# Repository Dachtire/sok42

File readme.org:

#+TITLE: Split Optical Keyboard
[[./hardware/image/00-overview.jpg]]

* Hardware
** MCU
gd32vf103cbt6

** Case
Stacked acrylic or 3d print

** Switch
gateron ks-22, ks-15

* Firmware
Custom firmware with usb, uart, led basic function

* Thanks
[[https://discord.com/channels/715975244896272618/715975245336412346][Optical Future]]

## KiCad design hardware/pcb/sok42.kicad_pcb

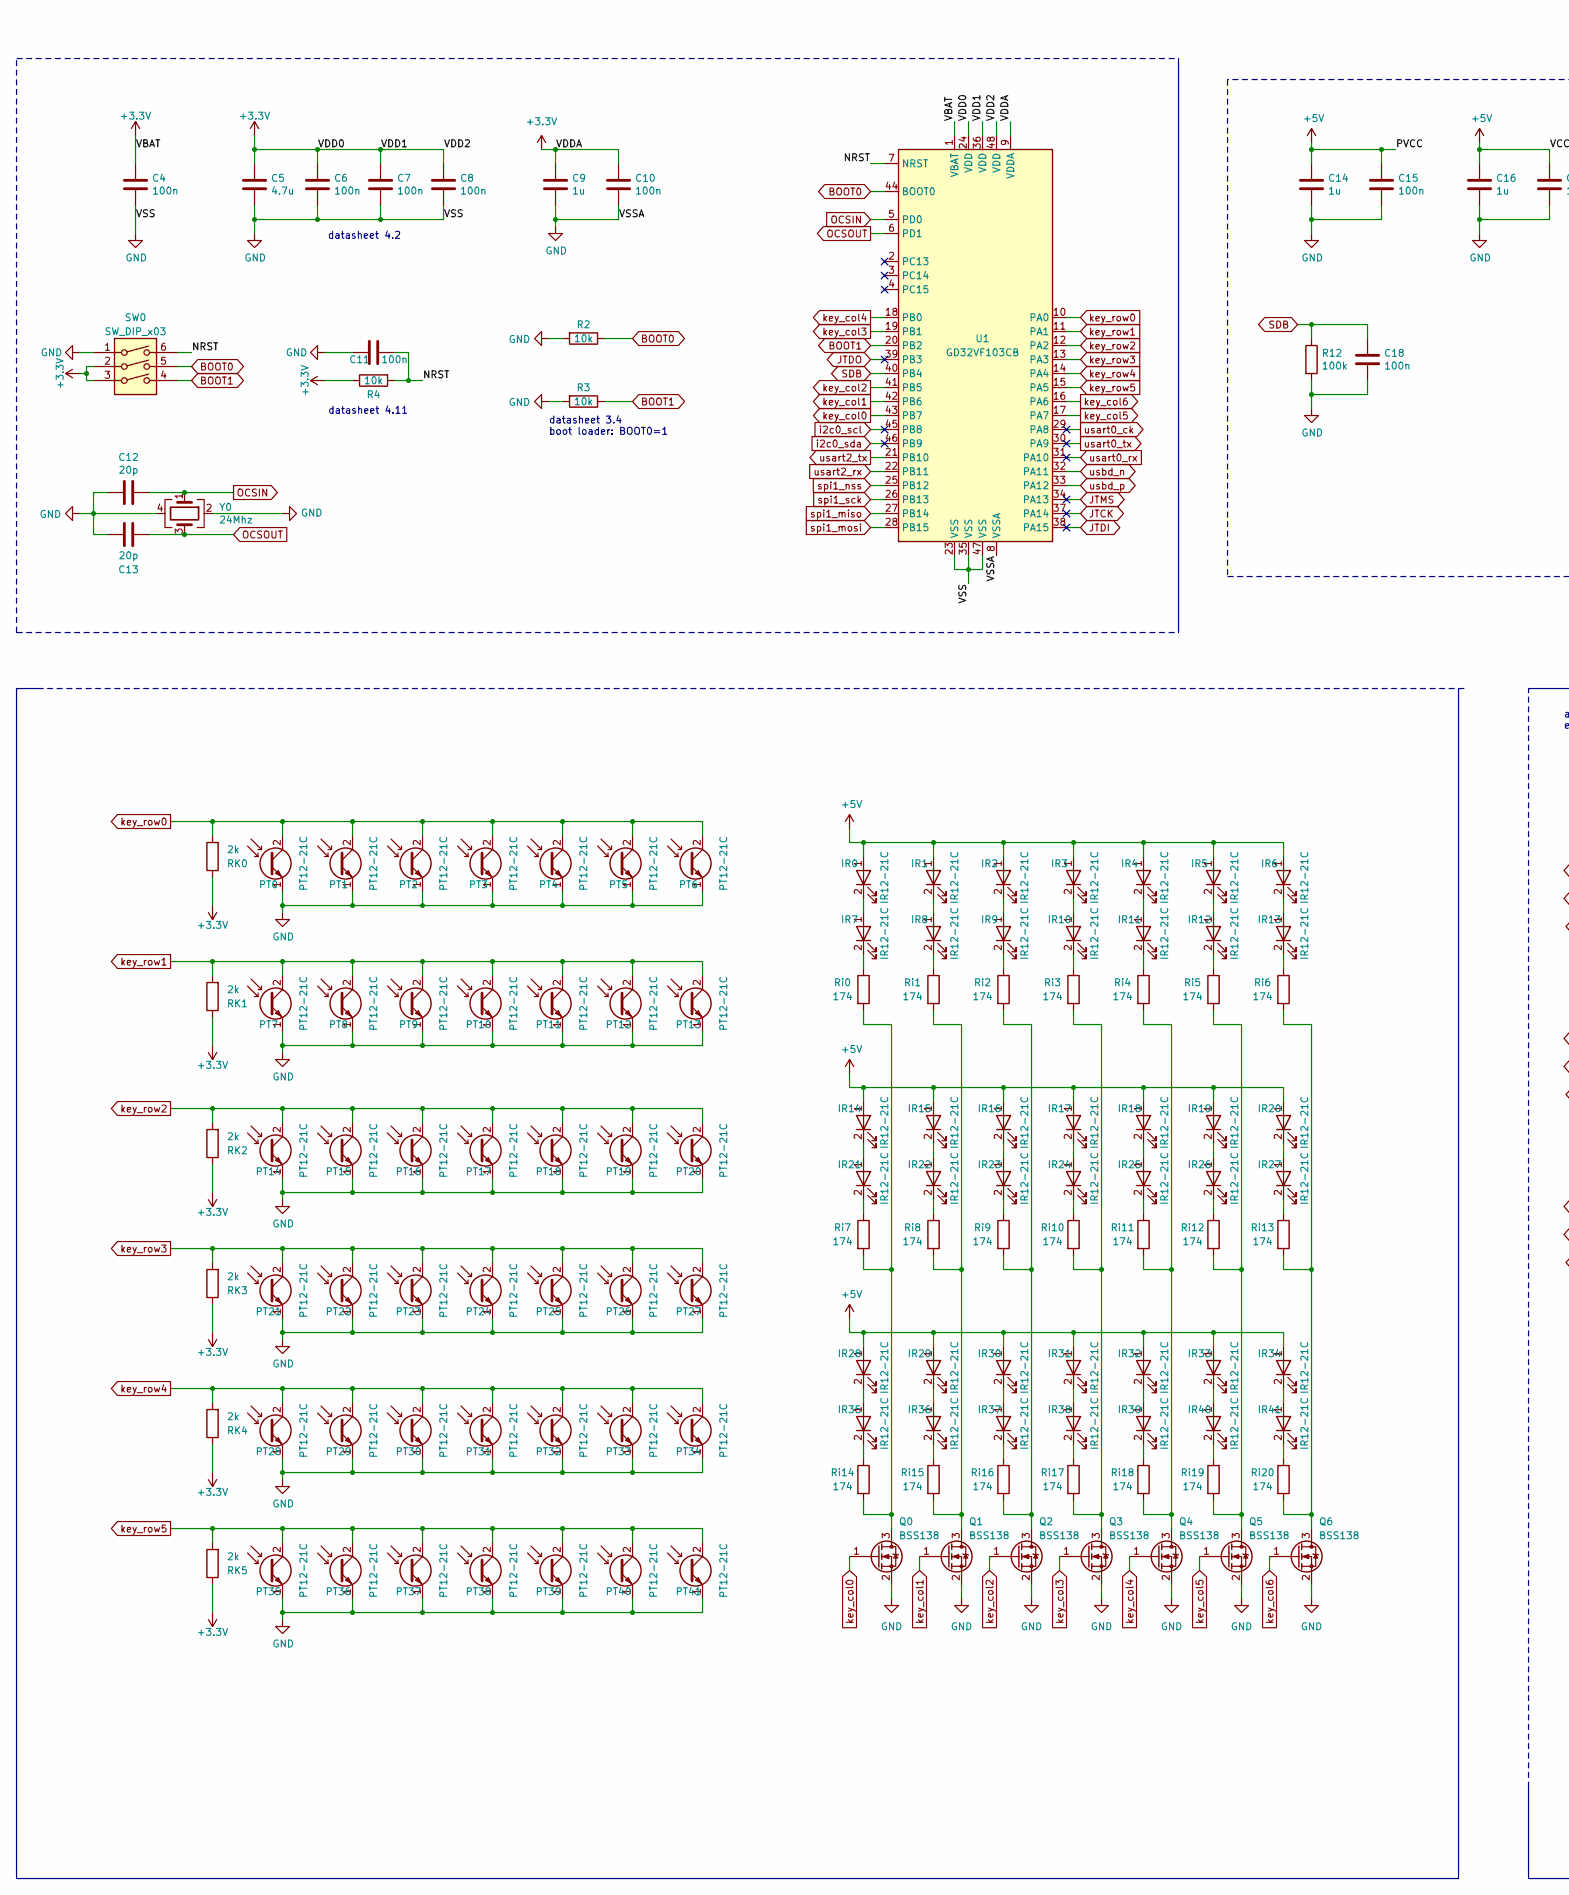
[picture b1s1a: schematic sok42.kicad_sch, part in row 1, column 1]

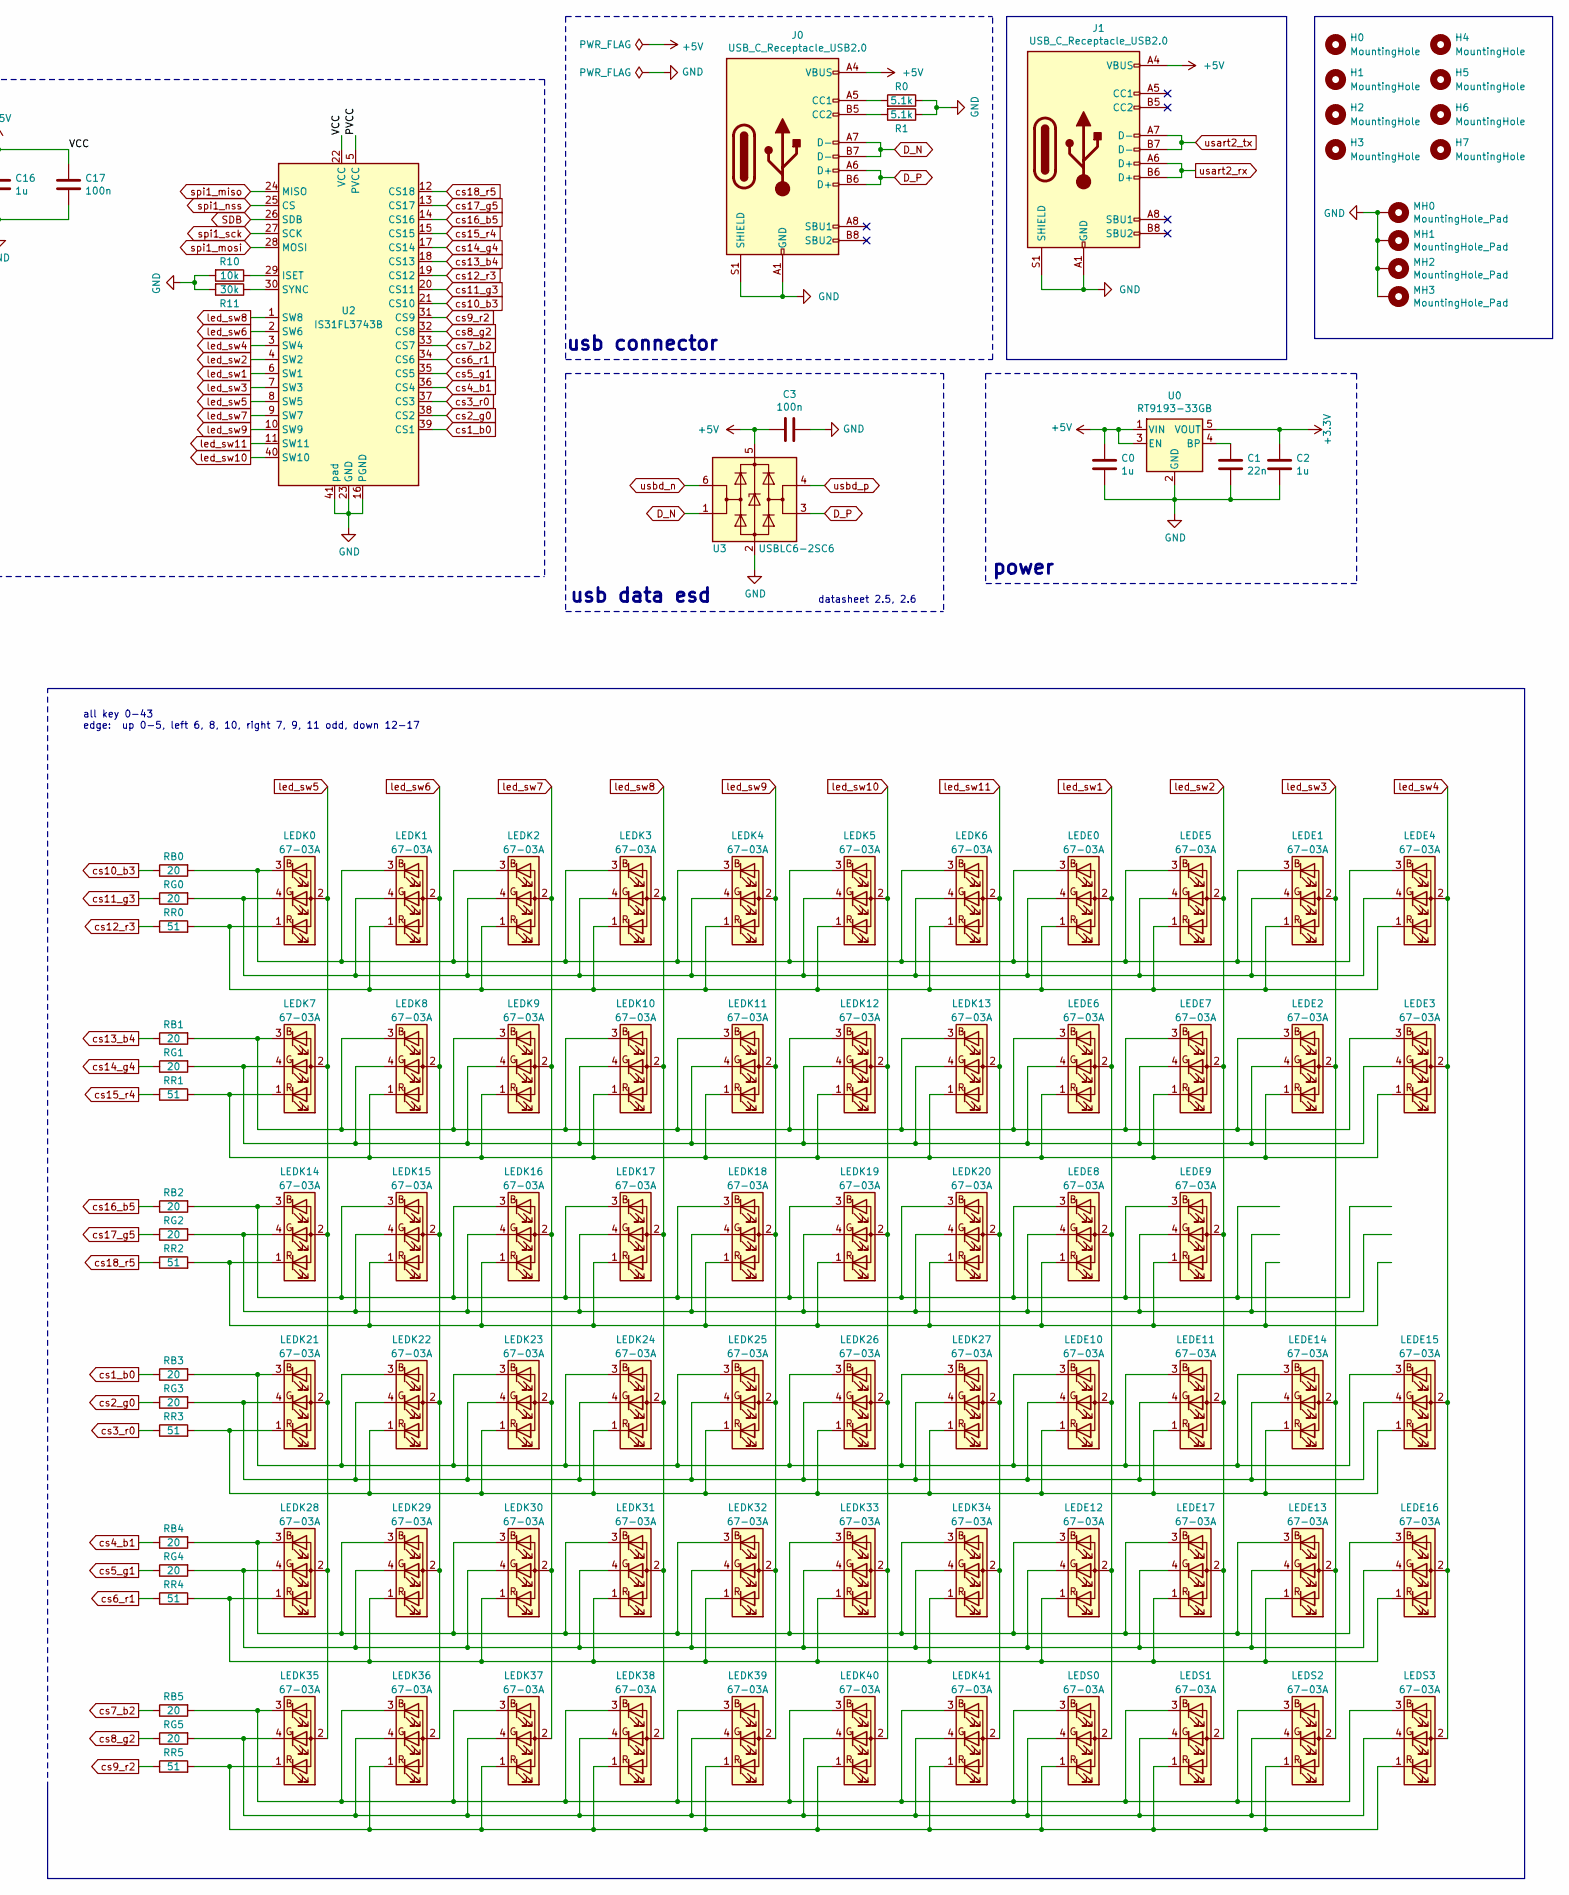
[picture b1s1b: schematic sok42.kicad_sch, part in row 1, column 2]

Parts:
C0, C2, C9, C14, C16: 1u; RC_0603_1608Metric
C1: 22n; RC_0603_1608Metric
C3, C4, C6, C7, C8, C10, C11, C15, C17, C18: 100n; RC_0603_1608Metric
C5: 4.7u; RC_1206_3216Metric
C12, C13: 20p; RC_0603_1608Metric
H0, H1, H2, H3, H4, H5, H6, H7: MountingHole
IR0, IR1, IR2, IR3, IR4, IR5, IR6, IR7, IR8, IR9, IR10, IR11, IR12, IR13, IR14, IR15, IR16, IR17, IR18, IR19, IR20, IR21, IR22, IR23, IR24, IR25, IR26, IR27, IR28, IR29, IR30, IR31, IR32, IR33, IR34, IR35, IR36, IR37, IR38, IR39, IR40, IR41: IR12-21C; 12-21-R
J0, J1: USB_C_Receptacle_USB2.0; USB_C_Receptacle_HRO_TYPE-C-31-M-12
LEDE0, LEDE1, LEDE2, LEDE3, LEDE4, LEDE5, LEDE6, LEDE7, LEDE8, LEDE9, LEDE10, LEDE11, LEDE12, LEDE13, LEDE14, LEDE15, LEDE16, LEDE17: 67-03A; LED_RGB_PLCC4
LEDK0, LEDK1, LEDK2, LEDK3, LEDK4, LEDK5, LEDK6, LEDK7, LEDK8, LEDK9, LEDK10, LEDK11, LEDK12, LEDK13, LEDK14, LEDK15, LEDK16, LEDK17, LEDK18, LEDK19, LEDK20, LEDK21, LEDK22, LEDK23, LEDK24, LEDK25, LEDK26, LEDK27, LEDK28, LEDK29, LEDK30, LEDK31, LEDK32, LEDK33, LEDK34, LEDK35, LEDK36, LEDK37, LEDK38, LEDK39, LEDK40, LEDK41: 67-03A; LED_RGB_PLCC4
LEDS0, LEDS1, LEDS2, LEDS3: 67-03A; LED_RGB_PLCC4
MH0, MH1, MH2, MH3: MountingHole_Pad
PT0, PT1, PT2, PT3, PT4, PT5, PT6, PT7, PT8, PT9, PT10, PT11, PT12, PT13, PT14, PT15, PT16, PT17, PT18, PT19, PT20, PT21, PT22, PT23, PT24, PT25, PT26, PT27, PT28, PT29, PT30, PT31, PT32, PT33, PT34, PT35, PT36, PT37, PT38, PT39, PT40, PT41: PT12-21C; 12-21-R
Q0, Q1, Q2, Q3, Q4, Q5, Q6: BSS138; SOT-23
R0, R1: 5.1k; RC_0603_1608Metric
R2, R3, R4, R10: 10k; RC_0603_1608Metric
R11: 30k; RC_0603_1608Metric
R12: 100k; RC_0603_1608Metric
RB0, RB1, RB2, RB3, RB4, RB5: 20; RC_0603_1608Metric
RG0, RG1, RG2, RG3, RG4, RG5: 20; RC_0603_1608Metric
RK0, RK1, RK2, RK3, RK4, RK5: 2k; RC_0603_1608Metric
RR0, RR1, RR2, RR3, RR4, RR5: 51; RC_0603_1608Metric
Ri0, Ri1, Ri2, Ri3, Ri4, Ri5, Ri6, Ri7, Ri8, Ri9, Ri10, Ri11, Ri12, Ri13, Ri14, Ri15, Ri16, Ri17, Ri18, Ri19, Ri20: 174; RC_0603_1608Metric
SW0: SW_DIP_x03; SW_DIP_SPSTx03_Slide_KingTek_DSHP03TS_W7.62mm_P1.27mm
U0: RT9193-33GB; SOT-23-5
U1: GD32VF103CB; LQFP-48_7x7mm_P0.5mm
U2: IS31FL3743B; UQFN-40-1EP_5x5mm_P0.4mm_EP3.4x3.4mm_ThermalVias
U3: USBLC6-2SC6; SOT-23-6
Y0: 24Mhz; Crystal_SMD_3225-4Pin_3.2x2.5mm

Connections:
+3.3V: C2.1, C4.1, C5.1, C6.1, C7.1, C8.1, C9.1, C10.1, R4.1, RK0.1, RK1.1, RK2.1, RK3.1, RK4.1, RK5.1, SW0.2, SW0.3, U0.5 (VOUT), U1.1 (VBAT), U1.9 (VDDA), U1.24 (VDD), U1.36 (VDD), U1.48 (VDD)
+5V: C0.1, C3.2, C14.1, C15.1, C16.1, C17.1, IR0.1 (A), IR1.1 (A), IR2.1 (A), IR3.1 (A), IR4.1 (A), IR5.1 (A), IR6.1 (A), IR14.1 (A), IR15.1 (A), IR16.1 (A), IR17.1 (A), IR18.1 (A), IR19.1 (A), IR20.1 (A), IR28.1 (A), IR29.1 (A), IR30.1 (A), IR31.1 (A), IR32.1 (A), IR33.1 (A), IR34.1 (A), J0.A4 (VBUS), J0.A9 (VBUS), J0.B4 (VBUS), J0.B9 (VBUS), J1.A4 (VBUS), J1.A9 (VBUS), J1.B4 (VBUS), J1.B9 (VBUS), U0.1 (VIN), U0.3 (EN), U2.5 (PVCC), U2.22 (VCC), U3.5 (VBUS)
/NRST: C11.1, R4.2, SW0.6, U1.7 (NRST)
BOOT0: R2.1, SW0.5, U1.44 (BOOT0)
BOOT1: R3.1, SW0.4, U1.20 (PB2)
D_N: J0.A7 (D-), J0.B7 (D-), U3.1 (I/O1)
D_P: J0.A6 (D+), J0.B6 (D+), U3.3 (I/O2)
GND: C0.2, C1.2, C2.2, C3.1, C4.2, C5.2, C6.2, C7.2, C8.2, C9.2, C10.2, C11.2, C12.2, C13.2, C14.2, C15.2, C16.2, C17.2, C18.2, J0.A1 (GND), J0.A12 (GND), J0.B1 (GND), J0.B12 (GND), J0.S1 (SHIELD), J1.A1 (GND), J1.A12 (GND), J1.B1 (GND), J1.B12 (GND), J1.S1 (SHIELD), MH0.1, MH1.1, MH2.1, MH3.1, PT0.1 (E), PT1.1 (E), PT2.1 (E), PT3.1 (E), PT4.1 (E), PT5.1 (E), PT6.1 (E), PT7.1 (E), PT8.1 (E), PT9.1 (E), PT10.1 (E), PT11.1 (E), PT12.1 (E), PT13.1 (E), PT14.1 (E), PT15.1 (E), PT16.1 (E), PT17.1 (E), PT18.1 (E), PT19.1 (E), PT20.1 (E), PT21.1 (E), PT22.1 (E), PT23.1 (E), PT24.1 (E), PT25.1 (E), PT26.1 (E), PT27.1 (E), PT28.1 (E), PT29.1 (E), PT30.1 (E), PT31.1 (E), PT32.1 (E), PT33.1 (E), PT34.1 (E), PT35.1 (E), PT36.1 (E), PT37.1 (E), PT38.1 (E), PT39.1 (E), PT40.1 (E), PT41.1 (E), Q0.2 (S), Q1.2 (S), Q2.2 (S), Q3.2 (S), Q4.2 (S), Q5.2 (S), Q6.2 (S), R0.1, R1.1, R2.2, R3.2, R10.2, R11.2, R12.2, SW0.1, U0.2 (GND), U1.8 (VSSA), U1.23 (VSS), U1.35 (VSS), U1.47 (VSS), U2.16 (PGND), U2.23 (GND), U2.41 (pad), U3.2 (GND), Y0.2, Y0.4
JTCK: U1.37 (PA14)
JTDI: U1.38 (PA15)
JTDO: U1.39 (PB3)
JTMS: U1.34 (PA13)
unnamed: C1.1, U0.4 (BP)
unnamed: IR0.2 (K), IR7.1 (A)
unnamed: IR1.2 (K), IR8.1 (A)
unnamed: IR2.2 (K), IR9.1 (A)
unnamed: IR7.2 (K), Ri0.1
unnamed: IR8.2 (K), Ri1.1
unnamed: IR9.2 (K), Ri2.1
unnamed: IR3.2 (K), IR10.1 (A)
unnamed: IR10.2 (K), Ri3.1
unnamed: IR4.2 (K), IR11.1 (A)
unnamed: IR11.2 (K), Ri4.1
unnamed: IR5.2 (K), IR12.1 (A)
unnamed: IR12.2 (K), Ri5.1
unnamed: IR6.2 (K), IR13.1 (A)
unnamed: IR13.2 (K), Ri6.1
unnamed: IR14.2 (K), IR21.1 (A)
unnamed: IR15.2 (K), IR22.1 (A)
unnamed: IR16.2 (K), IR23.1 (A)
unnamed: IR17.2 (K), IR24.1 (A)
unnamed: IR18.2 (K), IR25.1 (A)
unnamed: IR19.2 (K), IR26.1 (A)
unnamed: IR20.2 (K), IR27.1 (A)
unnamed: IR21.2 (K), Ri7.1
unnamed: IR22.2 (K), Ri8.1
unnamed: IR23.2 (K), Ri9.1
unnamed: IR24.2 (K), Ri10.1
unnamed: IR25.2 (K), Ri11.1
unnamed: IR26.2 (K), Ri12.1
unnamed: IR27.2 (K), Ri13.1
unnamed: IR28.2 (K), IR35.1 (A)
unnamed: IR29.2 (K), IR36.1 (A)
unnamed: IR30.2 (K), IR37.1 (A)
unnamed: IR31.2 (K), IR38.1 (A)
unnamed: IR32.2 (K), IR39.1 (A)
unnamed: IR33.2 (K), IR40.1 (A)
unnamed: IR34.2 (K), IR41.1 (A)
unnamed: IR35.2 (K), Ri14.1
unnamed: IR36.2 (K), Ri15.1
unnamed: IR37.2 (K), Ri16.1
unnamed: IR38.2 (K), Ri17.1
unnamed: IR39.2 (K), Ri18.1
unnamed: IR40.2 (K), Ri19.1
unnamed: IR41.2 (K), Ri20.1
unnamed: J0.A5 (CC1), R0.2
unnamed: J0.B5 (CC2), R1.2
unnamed: LEDE0.1 (RK), LEDE1.1 (RK), LEDE4.1 (RK), LEDE5.1 (RK), LEDK0.1 (RK), LEDK1.1 (RK), LEDK2.1 (RK), LEDK3.1 (RK), LEDK4.1 (RK), LEDK5.1 (RK), LEDK6.1 (RK), RR0.2
unnamed: LEDE0.3 (BK), LEDE1.3 (BK), LEDE4.3 (BK), LEDE5.3 (BK), LEDK0.3 (BK), LEDK1.3 (BK), LEDK2.3 (BK), LEDK3.3 (BK), LEDK4.3 (BK), LEDK5.3 (BK), LEDK6.3 (BK), RB0.2
unnamed: LEDE0.4 (GK), LEDE1.4 (GK), LEDE4.4 (GK), LEDE5.4 (GK), LEDK0.4 (GK), LEDK1.4 (GK), LEDK2.4 (GK), LEDK3.4 (GK), LEDK4.4 (GK), LEDK5.4 (GK), LEDK6.4 (GK), RG0.2
unnamed: LEDE2.1 (RK), LEDE3.1 (RK), LEDE6.1 (RK), LEDE7.1 (RK), LEDK7.1 (RK), LEDK8.1 (RK), LEDK9.1 (RK), LEDK10.1 (RK), LEDK11.1 (RK), LEDK12.1 (RK), LEDK13.1 (RK), RR1.2
unnamed: LEDE2.3 (BK), LEDE3.3 (BK), LEDE6.3 (BK), LEDE7.3 (BK), LEDK7.3 (BK), LEDK8.3 (BK), LEDK9.3 (BK), LEDK10.3 (BK), LEDK11.3 (BK), LEDK12.3 (BK), LEDK13.3 (BK), RB1.2
unnamed: LEDE2.4 (GK), LEDE3.4 (GK), LEDE6.4 (GK), LEDE7.4 (GK), LEDK7.4 (GK), LEDK8.4 (GK), LEDK9.4 (GK), LEDK10.4 (GK), LEDK11.4 (GK), LEDK12.4 (GK), LEDK13.4 (GK), RG1.2
unnamed: LEDE8.1 (RK), LEDE9.1 (RK), LEDK14.1 (RK), LEDK15.1 (RK), LEDK16.1 (RK), LEDK17.1 (RK), LEDK18.1 (RK), LEDK19.1 (RK), LEDK20.1 (RK), RR2.2
unnamed: LEDE8.3 (BK), LEDE9.3 (BK), LEDK14.3 (BK), LEDK15.3 (BK), LEDK16.3 (BK), LEDK17.3 (BK), LEDK18.3 (BK), LEDK19.3 (BK), LEDK20.3 (BK), RB2.2
unnamed: LEDE8.4 (GK), LEDE9.4 (GK), LEDK14.4 (GK), LEDK15.4 (GK), LEDK16.4 (GK), LEDK17.4 (GK), LEDK18.4 (GK), LEDK19.4 (GK), LEDK20.4 (GK), RG2.2
unnamed: LEDE10.1 (RK), LEDE11.1 (RK), LEDE14.1 (RK), LEDE15.1 (RK), LEDK21.1 (RK), LEDK22.1 (RK), LEDK23.1 (RK), LEDK24.1 (RK), LEDK25.1 (RK), LEDK26.1 (RK), LEDK27.1 (RK), RR3.2
unnamed: LEDE10.3 (BK), LEDE11.3 (BK), LEDE14.3 (BK), LEDE15.3 (BK), LEDK21.3 (BK), LEDK22.3 (BK), LEDK23.3 (BK), LEDK24.3 (BK), LEDK25.3 (BK), LEDK26.3 (BK), LEDK27.3 (BK), RB3.2
unnamed: LEDE10.4 (GK), LEDE11.4 (GK), LEDE14.4 (GK), LEDE15.4 (GK), LEDK21.4 (GK), LEDK22.4 (GK), LEDK23.4 (GK), LEDK24.4 (GK), LEDK25.4 (GK), LEDK26.4 (GK), LEDK27.4 (GK), RG3.2
unnamed: LEDE12.1 (RK), LEDE13.1 (RK), LEDE16.1 (RK), LEDE17.1 (RK), LEDK28.1 (RK), LEDK29.1 (RK), LEDK30.1 (RK), LEDK31.1 (RK), LEDK32.1 (RK), LEDK33.1 (RK), LEDK34.1 (RK), RR4.2
unnamed: LEDE12.3 (BK), LEDE13.3 (BK), LEDE16.3 (BK), LEDE17.3 (BK), LEDK28.3 (BK), LEDK29.3 (BK), LEDK30.3 (BK), LEDK31.3 (BK), LEDK32.3 (BK), LEDK33.3 (BK), LEDK34.3 (BK), RB4.2
unnamed: LEDE12.4 (GK), LEDE13.4 (GK), LEDE16.4 (GK), LEDE17.4 (GK), LEDK28.4 (GK), LEDK29.4 (GK), LEDK30.4 (GK), LEDK31.4 (GK), LEDK32.4 (GK), LEDK33.4 (GK), LEDK34.4 (GK), RG4.2
unnamed: LEDK35.1 (RK), LEDK36.1 (RK), LEDK37.1 (RK), LEDK38.1 (RK), LEDK39.1 (RK), LEDK40.1 (RK), LEDK41.1 (RK), LEDS0.1 (RK), LEDS1.1 (RK), LEDS2.1 (RK), LEDS3.1 (RK), RR5.2
unnamed: LEDK35.3 (BK), LEDK36.3 (BK), LEDK37.3 (BK), LEDK38.3 (BK), LEDK39.3 (BK), LEDK40.3 (BK), LEDK41.3 (BK), LEDS0.3 (BK), LEDS1.3 (BK), LEDS2.3 (BK), LEDS3.3 (BK), RB5.2
unnamed: LEDK35.4 (GK), LEDK36.4 (GK), LEDK37.4 (GK), LEDK38.4 (GK), LEDK39.4 (GK), LEDK40.4 (GK), LEDK41.4 (GK), LEDS0.4 (GK), LEDS1.4 (GK), LEDS2.4 (GK), LEDS3.4 (GK), RG5.2
unnamed: Q0.3 (D), Ri0.2, Ri7.2, Ri14.2
unnamed: Q1.3 (D), Ri1.2, Ri8.2, Ri15.2
unnamed: Q2.3 (D), Ri2.2, Ri9.2, Ri16.2
unnamed: Q3.3 (D), Ri3.2, Ri10.2, Ri17.2
unnamed: Q4.3 (D), Ri4.2, Ri11.2, Ri18.2
unnamed: Q5.3 (D), Ri5.2, Ri12.2, Ri19.2
unnamed: Q6.3 (D), Ri6.2, Ri13.2, Ri20.2
unnamed: R10.1, U2.29 (ISET)
unnamed: R11.1, U2.30 (SYNC)
OCSIN: C12.1, U1.5 (PD0), Y0.1
OCSOUT: C13.1, U1.6 (PD1), Y0.3
SDB: C18.1, R12.1, U1.40 (PB4), U2.26 (SDB)
cs1_b0: RB3.1, U2.39 (CS1)
cs2_g0: RG3.1, U2.38 (CS2)
cs3_r0: RR3.1, U2.37 (CS3)
cs4_b1: RB4.1, U2.36 (CS4)
cs5_g1: RG4.1, U2.35 (CS5)
cs6_r1: RR4.1, U2.34 (CS6)
cs7_b2: RB5.1, U2.33 (CS7)
cs8_g2: RG5.1, U2.32 (CS8)
cs9_r2: RR5.1, U2.31 (CS9)
cs10_b3: RB0.1, U2.21 (CS10)
cs11_g3: RG0.1, U2.20 (CS11)
cs12_r3: RR0.1, U2.19 (CS12)
cs13_b4: RB1.1, U2.18 (CS13)
cs14_g4: RG1.1, U2.17 (CS14)
cs15_r4: RR1.1, U2.15 (CS15)
cs16_b5: RB2.1, U2.14 (CS16)
cs17_g5: RG2.1, U2.13 (CS17)
cs18_r5: RR2.1, U2.12 (CS18)
i2c0_scl: U1.45 (PB8)
i2c0_sda: U1.46 (PB9)
key_col0: Q0.1 (G), U1.43 (PB7)
key_col1: Q1.1 (G), U1.42 (PB6)
key_col2: Q2.1 (G), U1.41 (PB5)
key_col3: Q3.1 (G), U1.19 (PB1)
key_col4: Q4.1 (G), U1.18 (PB0)
key_col5: Q5.1 (G), U1.17 (PA7)
key_col6: Q6.1 (G), U1.16 (PA6)
key_row0: PT0.2 (C), PT1.2 (C), PT2.2 (C), PT3.2 (C), PT4.2 (C), PT5.2 (C), PT6.2 (C), RK0.2, U1.10 (PA0)
key_row1: PT7.2 (C), PT8.2 (C), PT9.2 (C), PT10.2 (C), PT11.2 (C), PT12.2 (C), PT13.2 (C), RK1.2, U1.11 (PA1)
key_row2: PT14.2 (C), PT15.2 (C), PT16.2 (C), PT17.2 (C), PT18.2 (C), PT19.2 (C), PT20.2 (C), RK2.2, U1.12 (PA2)
key_row3: PT21.2 (C), PT22.2 (C), PT23.2 (C), PT24.2 (C), PT25.2 (C), PT26.2 (C), PT27.2 (C), RK3.2, U1.13 (PA3)
key_row4: PT28.2 (C), PT29.2 (C), PT30.2 (C), PT31.2 (C), PT32.2 (C), PT33.2 (C), PT34.2 (C), RK4.2, U1.14 (PA4)
key_row5: PT35.2 (C), PT36.2 (C), PT37.2 (C), PT38.2 (C), PT39.2 (C), PT40.2 (C), PT41.2 (C), RK5.2, U1.15 (PA5)
led_sw1: LEDE0.2 (A), LEDE6.2 (A), LEDE8.2 (A), LEDE10.2 (A), LEDE12.2 (A), LEDS0.2 (A), U2.6 (SW1)
led_sw2: LEDE5.2 (A), LEDE7.2 (A), LEDE9.2 (A), LEDE11.2 (A), LEDE17.2 (A), LEDS1.2 (A), U2.4 (SW2)
led_sw3: LEDE1.2 (A), LEDE2.2 (A), LEDE13.2 (A), LEDE14.2 (A), LEDS2.2 (A), U2.7 (SW3)
led_sw4: LEDE3.2 (A), LEDE4.2 (A), LEDE15.2 (A), LEDE16.2 (A), LEDS3.2 (A), U2.3 (SW4)
led_sw5: LEDK0.2 (A), LEDK7.2 (A), LEDK14.2 (A), LEDK21.2 (A), LEDK28.2 (A), LEDK35.2 (A), U2.8 (SW5)
led_sw6: LEDK1.2 (A), LEDK8.2 (A), LEDK15.2 (A), LEDK22.2 (A), LEDK29.2 (A), LEDK36.2 (A), U2.2 (SW6)
led_sw7: LEDK2.2 (A), LEDK9.2 (A), LEDK16.2 (A), LEDK23.2 (A), LEDK30.2 (A), LEDK37.2 (A), U2.9 (SW7)
led_sw8: LEDK3.2 (A), LEDK10.2 (A), LEDK17.2 (A), LEDK24.2 (A), LEDK31.2 (A), LEDK38.2 (A), U2.1 (SW8)
led_sw9: LEDK4.2 (A), LEDK11.2 (A), LEDK18.2 (A), LEDK25.2 (A), LEDK32.2 (A), LEDK39.2 (A), U2.10 (SW9)
led_sw10: LEDK5.2 (A), LEDK12.2 (A), LEDK19.2 (A), LEDK26.2 (A), LEDK33.2 (A), LEDK40.2 (A), U2.40 (SW10)
led_sw11: LEDK6.2 (A), LEDK13.2 (A), LEDK20.2 (A), LEDK27.2 (A), LEDK34.2 (A), LEDK41.2 (A), U2.11 (SW11)
spi1_miso: U1.27 (PB14), U2.24 (MISO)
spi1_mosi: U1.28 (PB15), U2.28 (MOSI)
spi1_nss: U1.25 (PB12), U2.25 (CS)
spi1_sck: U1.26 (PB13), U2.27 (SCK)
usart0_ck: U1.29 (PA8)
usart0_rx: U1.31 (PA10)
usart0_tx: U1.30 (PA9)
usart2_rx: J1.A6 (D+), J1.B6 (D+), U1.22 (PB11)
usart2_tx: J1.A7 (D-), J1.B7 (D-), U1.21 (PB10)
usbd_n: U1.32 (PA11), U3.6 (I/O1)
usbd_p: U1.33 (PA12), U3.4 (I/O2)

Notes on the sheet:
datasheet 2.5, 2.6
all key 0-43 edge: up 0-5, left 6, 8, 10, right 7, 9, 11 odd, down 12-17
usb data esd
datasheet 3.4 boot loader: BOOT0=1
datasheet 4.11
usb connector
power
datasheet 4.2

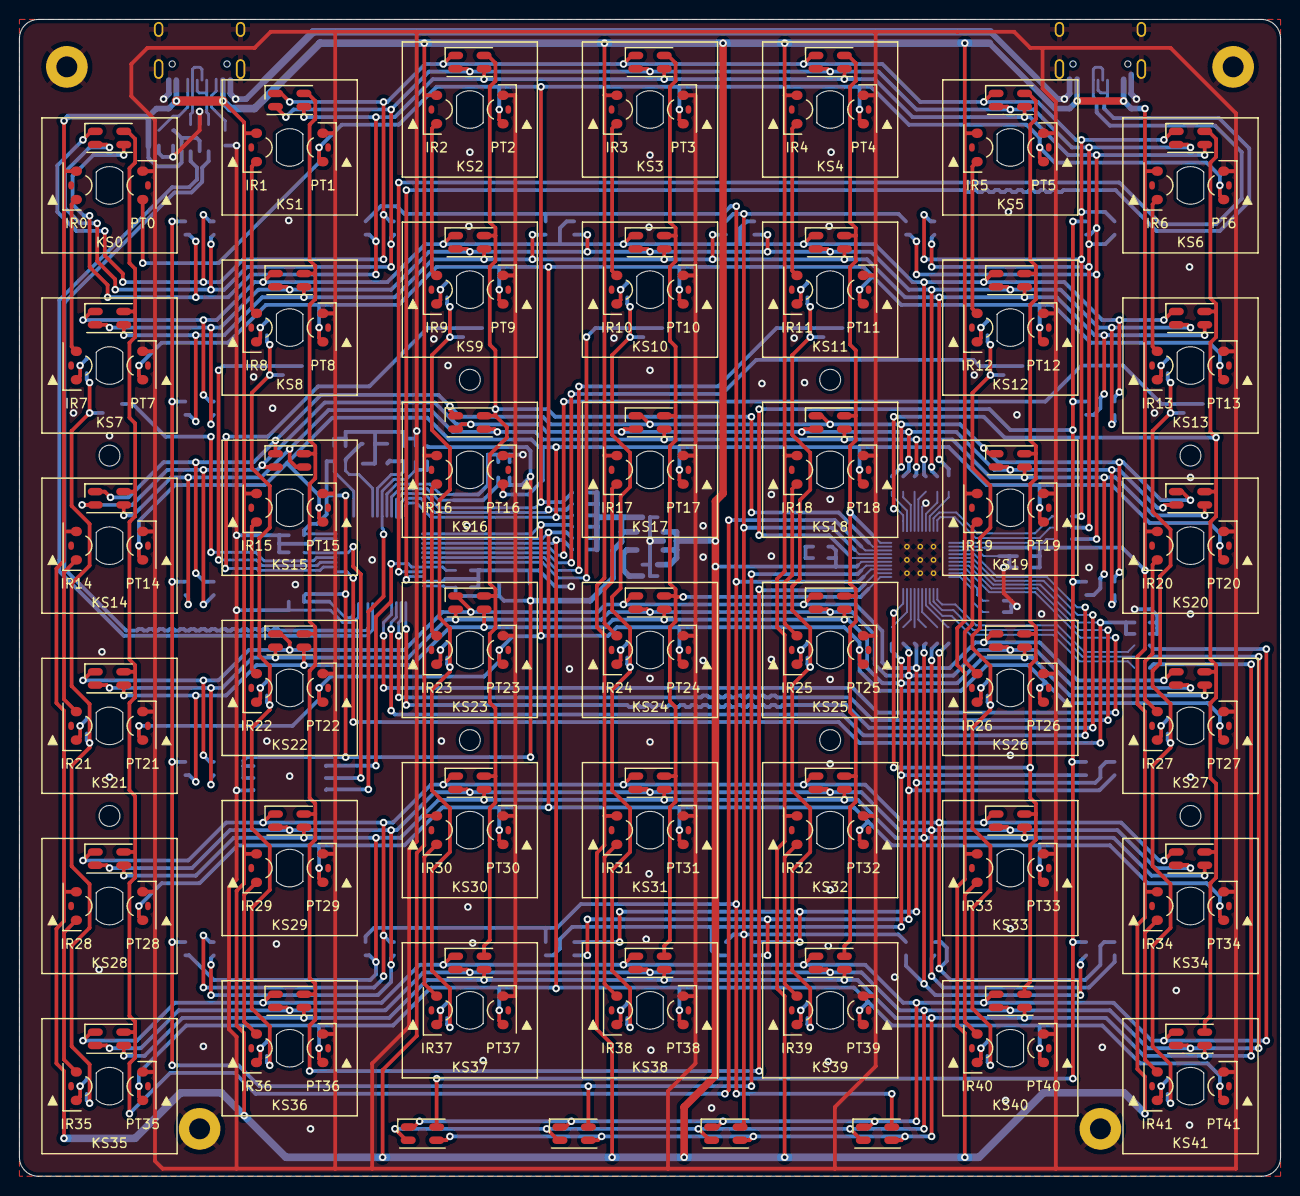
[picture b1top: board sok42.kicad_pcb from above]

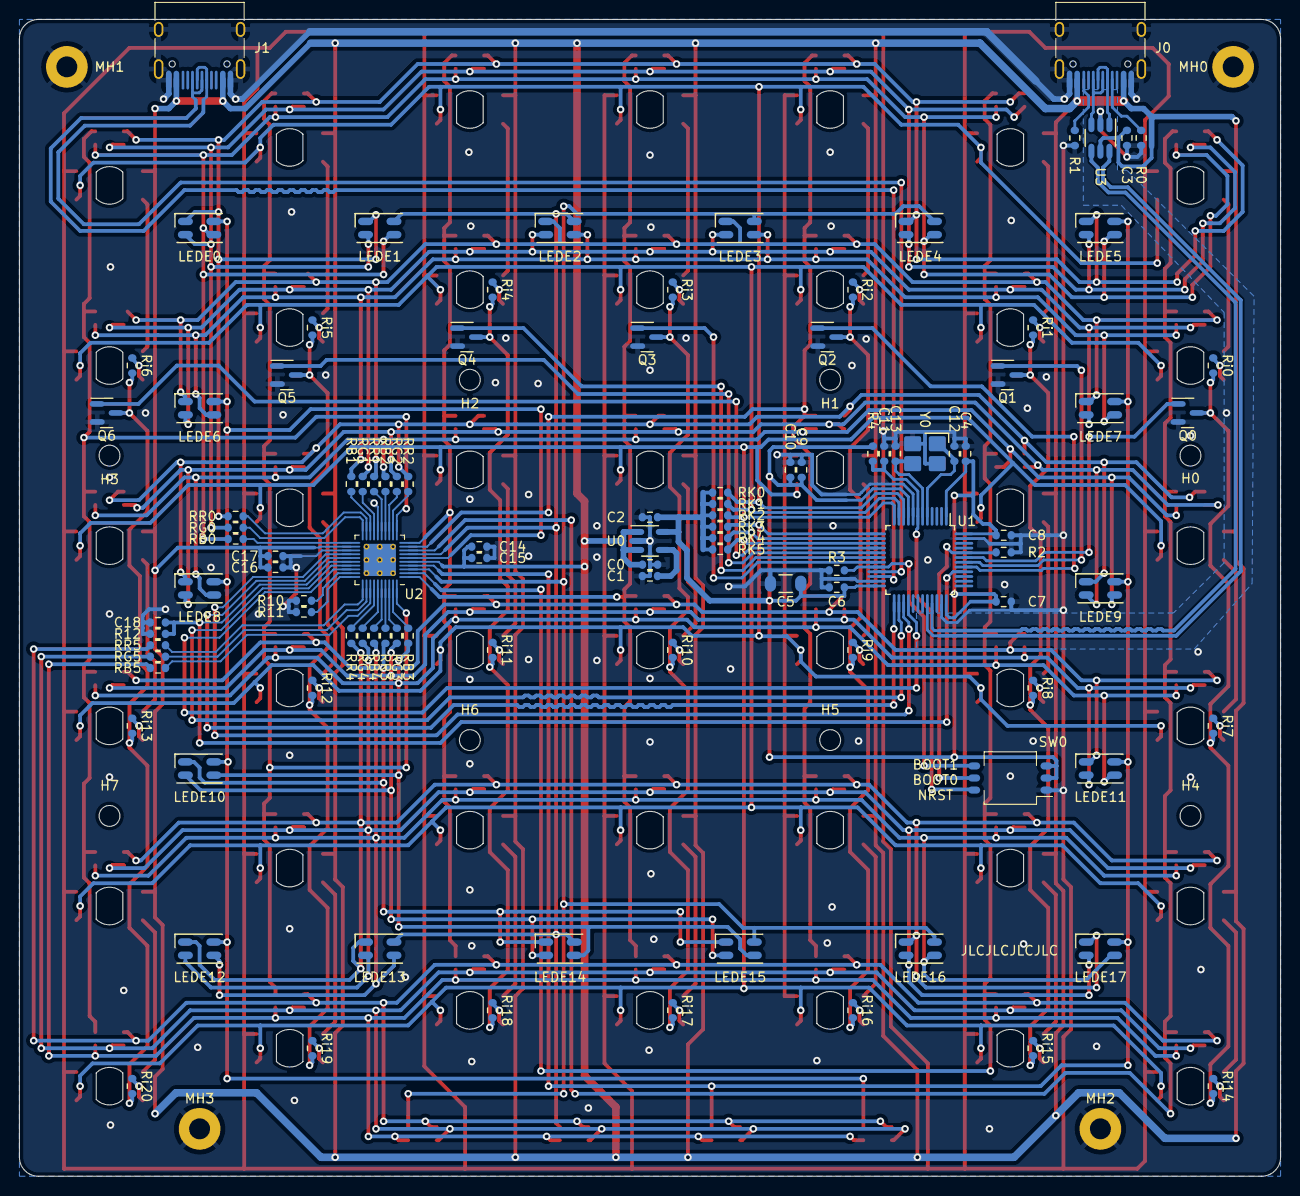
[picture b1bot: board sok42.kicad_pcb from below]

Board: 2 copper layers, 133.0 x 122.0 mm, 289 parts (117 on the bottom side), 133 nets.

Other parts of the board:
KS0, KS1, KS2, KS3, KS4, KS5, KS6, KS7, KS8, KS9, KS10, KS11, KS12, KS13, KS14, KS15, KS16, KS17, KS18, KS19, KS20, KS21, KS22, KS23, KS24, KS25, KS26, KS27, KS28, KS29, KS30, KS31, KS32, KS33, KS34, KS35, KS36, KS37, KS38, KS39, KS40, KS41: Gateron_KS_15_1.00u_PCB; KS-15

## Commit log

2022-07-23 v0.3.0
    add (firmware):
    system: 24Mhz HXTAL for 96Mhz system clock
    usb: hid keyborad
    feat (keyboard):
    uart dma communication
    multiple layers
